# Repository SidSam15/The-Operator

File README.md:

# The Operator

The Operator is a 4 key macropad with a rotary encoder, an OLED Display, and 16 LED's for underglow. It used KMK firmware.

This is my first macropad (and my first hardware project for Hack club ever!) and its purpose is to make the task of opening applications quicker, alongside looking cool. It works with hotkeys on my laptop to open applications like Fusion, Bambu Studio, VS Code, and Google at the click of a button, plus it controls volume and its LEDs with a Rotary Encoder. The OLED shows the last button clicked and it shows the on/off status of the LEDs. This project has helped me learn a lot, particularly in PCB design.

To use this, simply connect it to power via the USB-C on the XIAO 2040 and use like any other macropad.

## Features:
- Although only be visible once printed, the bottom layer uses clear filament to diffuse underglow and has a filleted bottom as tonot detract from the look of the black filament used in the top two layers.
- 128x32 OLED Display.
- EC11 Rotary encoder for volume and LED power. 
- 16 WS2812B RGB LEDs for underglow. Don't worry, their power is limited in firmware.
- 4 Keys.

## CAD Model:
Everything fits together using 4 M3 screws and heatset inserts. The screws go into the hols along the edges of the case

Case:

It has 3 separate printed pieces. The clear bottom where the PCB sits, the middle, and the top.

Full CAD:

Made in Fusion360.

## PCB:
This PCB was made in KiCad, and all the components of the silkscreen were downloaded from the web and manually added inside of KiCad.

Schematic

PCB

I used MX_V1 for the keyswitch footprints, the generic footprint for the XIAO 2040, a 4-pin header for the OLED, the footprint from the guide for the rotary encoder, and the SK6812MINI-E for the LED footprints.

## Firmware Overview:
This hackpad uses KMK firmware for everything. 

- the rotary encoder changes volume. press to turn off LEDs.
- The 4 keys open applications by correlating with hotkeys on my laptop. Starting from the furthest left, they open Fusion, Bambu Studio, VS Code, and Google, respectivley. 
- The OLED shows the last key pressed and the LED on/off status.

In the future I really want to do more with the rotary encoder. I want to remove te volume feature and instead have it work with scripts on my laptop to preform a different function for each application (e.g, in VS turning would scroll, while pressing would run code, while in fusion, turning would do a 360 degree pan, while pressing would bring the veiw to home).

## BOM:
Everything needed to make this hackpad (aside from soldering iron and 3D printing things) can be found in the kit.

- 4x Cherry MX Switches
- 4x DSA Keycaps
- 4x M3x5x4 Heatset inserts
- 4x M3x16mm screws
- 16x WS2812B LEDs
- 1x 0.91" 128x32 OLED Display
- 1x EC11 Rotary Encoder
- 1x XIAO RP2040
- 1x Case (3 printed parts, one in clear filament the rest in black)

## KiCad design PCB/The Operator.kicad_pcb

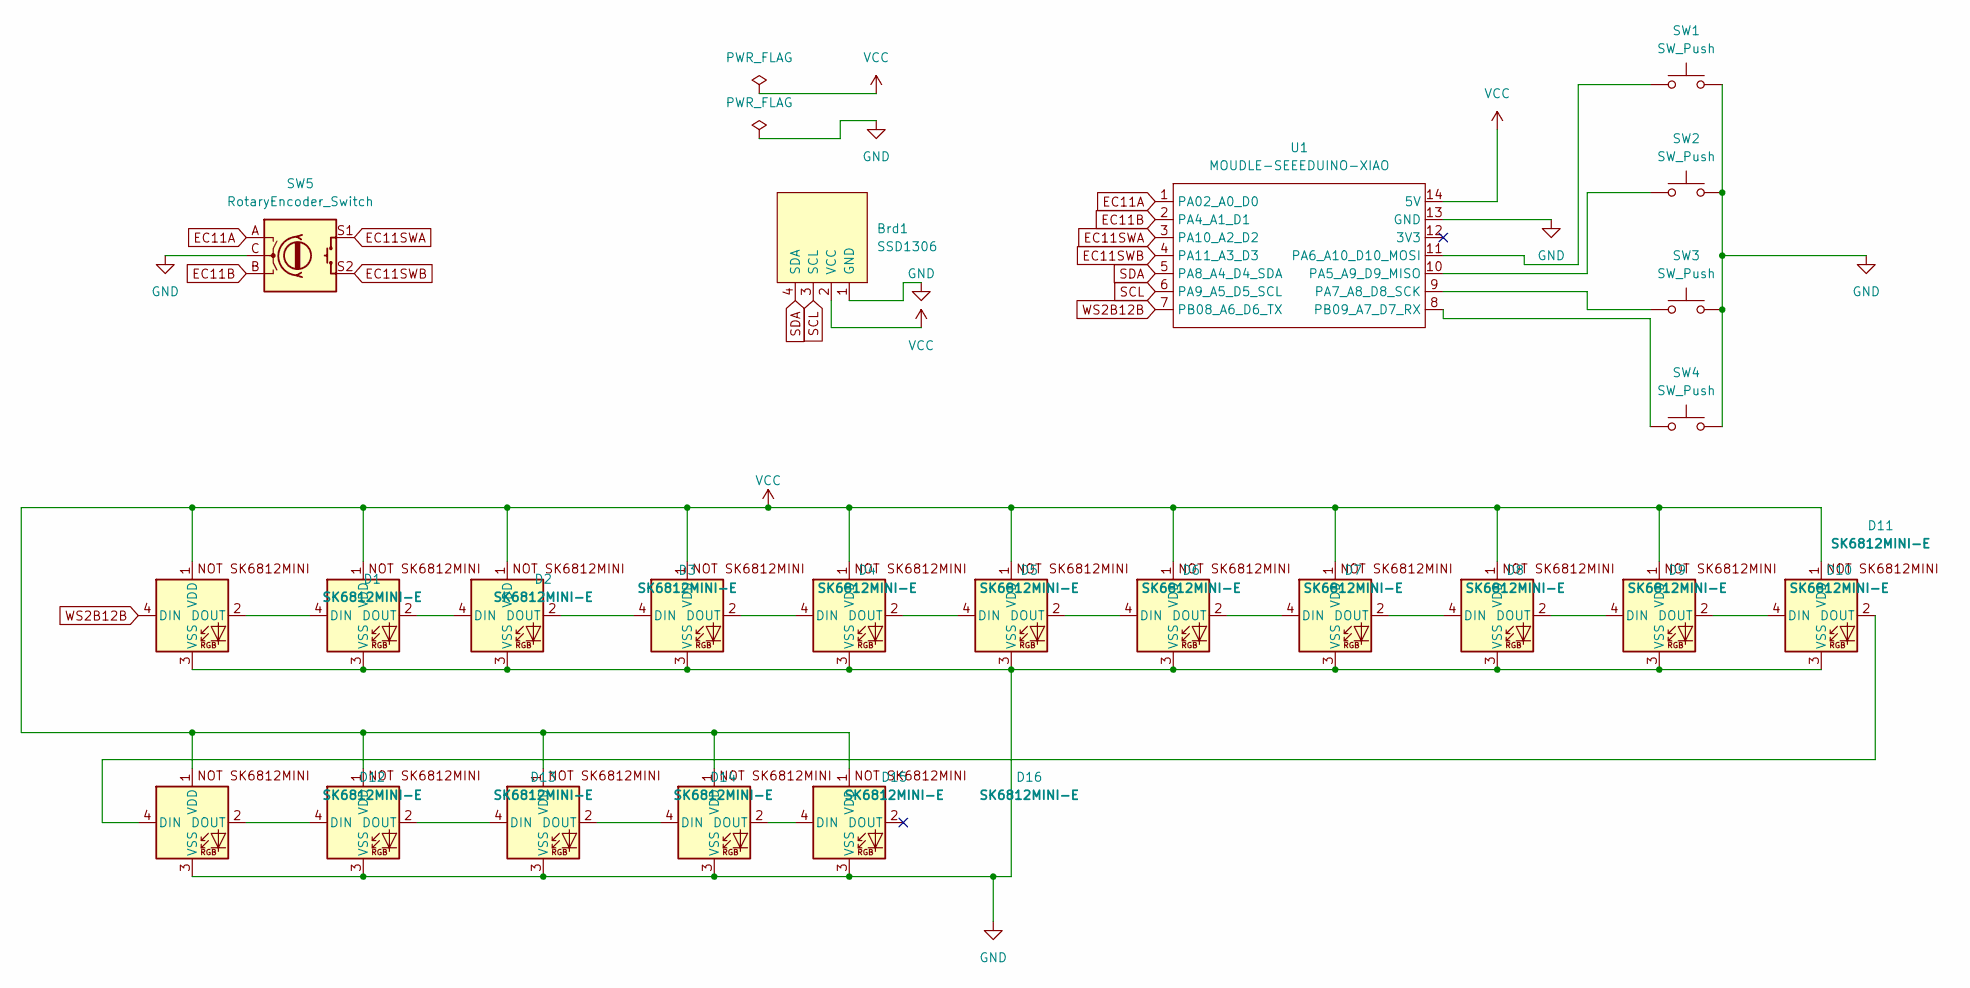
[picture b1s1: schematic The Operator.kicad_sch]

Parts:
Brd1: SSD1306; PinHeader_1x04_P2.54mm_Vertical
D1, D2, D3, D4, D5, D6, D7, D8, D9, D10, D11, D12, D13, D14, D15, D16: SK6812MINI-E; SK6812MINI-E_fixed
SW1, SW2, SW3, SW4: SW_Push; SW_Cherry_MX_1.00u_PCB
SW5: RotaryEncoder_Switch; RotaryEncoder_Alps_EC11E-Switch_Vertical_H20mm
U1: MOUDLE-SEEEDUINO-XIAO; XIAO-Generic-Hybrid-14P-2.54-21X17.8MM

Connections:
EC11A: SW5.A, U1.1 (PA02_A0_D0)
EC11B: SW5.B, U1.2 (PA4_A1_D1)
EC11SWA: SW5.S1, U1.3 (PA10_A2_D2)
EC11SWB: SW5.S2, U1.4 (PA11_A3_D3)
GND: Brd1.1 (GND), D1.3 (VSS), D2.3 (VSS), D3.3 (VSS), D4.3 (VSS), D5.3 (VSS), D6.3 (VSS), D7.3 (VSS), D8.3 (VSS), D9.3 (VSS), D10.3 (VSS), D11.3 (VSS), D12.3 (VSS), D13.3 (VSS), D14.3 (VSS), D15.3 (VSS), D16.3 (VSS), SW1.2, SW2.2, SW3.2, SW4.2, SW5.C, U1.13 (GND)
unnamed: D1.2 (DOUT), D2.4 (DIN)
unnamed: D2.2 (DOUT), D3.4 (DIN)
unnamed: D3.2 (DOUT), D4.4 (DIN)
unnamed: D4.2 (DOUT), D5.4 (DIN)
unnamed: D5.2 (DOUT), D6.4 (DIN)
unnamed: D6.2 (DOUT), D7.4 (DIN)
unnamed: D7.2 (DOUT), D8.4 (DIN)
unnamed: D8.2 (DOUT), D9.4 (DIN)
unnamed: D9.2 (DOUT), D10.4 (DIN)
unnamed: D10.2 (DOUT), D11.4 (DIN)
unnamed: D11.2 (DOUT), D12.4 (DIN)
unnamed: D12.2 (DOUT), D13.4 (DIN)
unnamed: D13.2 (DOUT), D14.4 (DIN)
unnamed: D14.2 (DOUT), D15.4 (DIN)
unnamed: D15.2 (DOUT), D16.4 (DIN)
unnamed: SW2.1, U1.10 (PA5_A9_D9_MISO)
unnamed: SW1.1, U1.11 (PA6_A10_D10_MOSI)
unnamed: SW3.1, U1.9 (PA7_A8_D8_SCK)
unnamed: SW4.1, U1.8 (PB09_A7_D7_RX)
SCL: Brd1.3 (SCL), U1.6 (PA9_A5_D5_SCL)
SDA: Brd1.4 (SDA), U1.5 (PA8_A4_D4_SDA)
VCC: Brd1.2 (VCC), D1.1 (VDD), D2.1 (VDD), D3.1 (VDD), D4.1 (VDD), D5.1 (VDD), D6.1 (VDD), D7.1 (VDD), D8.1 (VDD), D9.1 (VDD), D10.1 (VDD), D11.1 (VDD), D12.1 (VDD), D13.1 (VDD), D14.1 (VDD), D15.1 (VDD), D16.1 (VDD), U1.14 (5V)
WS2B12B: D1.4 (DIN), U1.7 (PB08_A6_D6_TX)

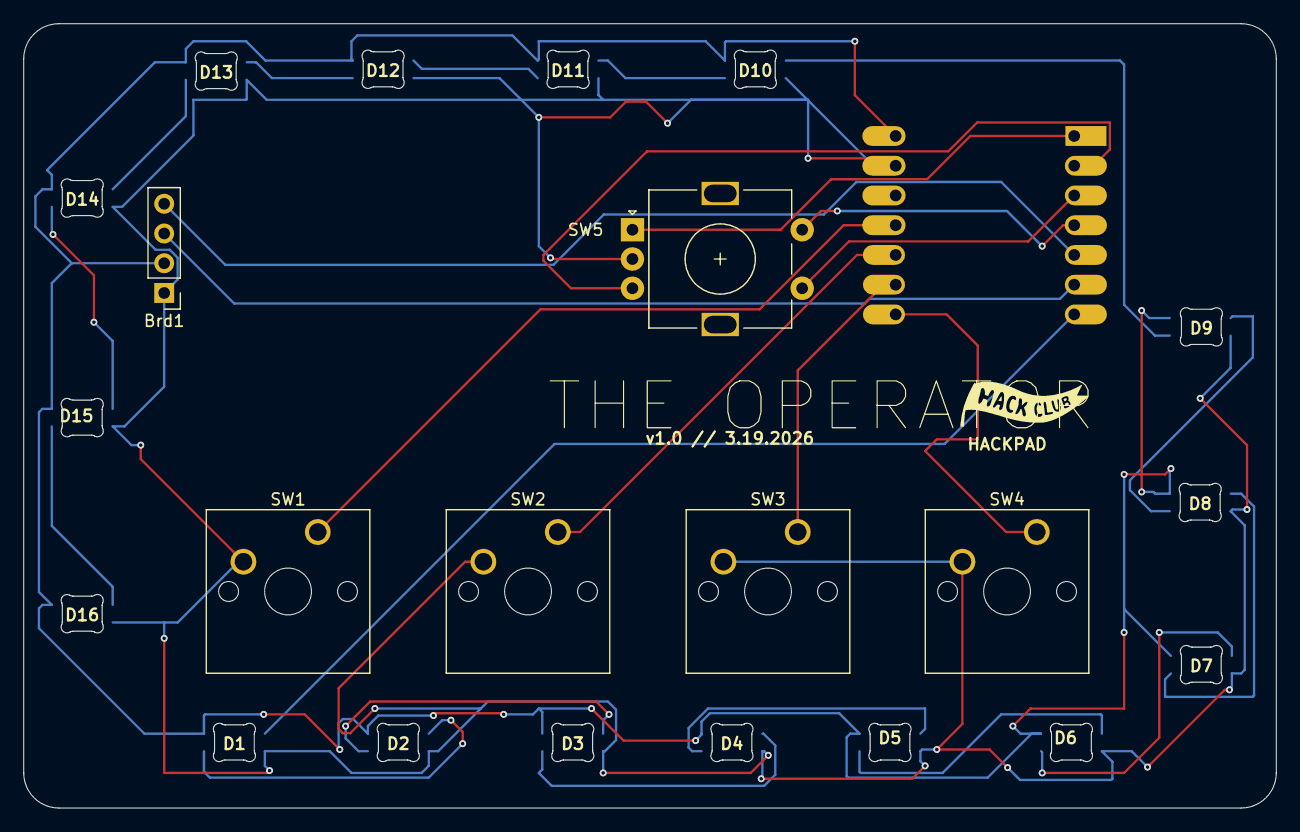
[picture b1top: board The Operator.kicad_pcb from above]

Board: 2 copper layers, 107.0 x 67.0 mm, 23 parts (1 on the bottom side), 28 nets.

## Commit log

2026-03-22 everything
2026-03-22 excess file
2026-03-22 read me
2026-03-22 .png
2026-03-22 stff
2026-03-22 fixed leds
2026-03-22 readme
2026-03-22 cleanup
2026-03-22 Replace schematic and PCB images with new versions
    Updated schematic and PCB images in README.
2026-03-22 fixed oled
2026-03-22 Update README with new PCB image
    Added a new PCB image to the README.
2026-03-22 deleted some files
2026-03-22 stuff
2026-03-22 gerber
